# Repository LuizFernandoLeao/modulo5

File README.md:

# Semana 1

Atalho para a página pessoal: [link](https://github.com/LuizFernandoLeao/modulo5/blob/main/semana1/src/pages/my-markdown-page.md)

# Website

This website is built using [Docusaurus](https://docusaurus.io/), a modern static website generator.

### Installation

```
$ yarn
```

### Local Development

```
$ yarn start
```

This command starts a local development server and opens up a browser window. Most changes are reflected live without having to restart the server.

### Build

```
$ yarn build
```

This command generates static content into the `build` directory and can be served using any static contents hosting service.

### Deployment

Using SSH:

```
$ USE_SSH=true yarn deploy
```

Not using SSH:

```
$ GIT_USER=<Your GitHub username> yarn deploy
```

If you are using GitHub pages for hosting, this command is a convenient way to build the website and push to the `gh-pages` branch.

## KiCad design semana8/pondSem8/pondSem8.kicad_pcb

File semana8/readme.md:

# Atividade Ponderada - PCB c/ Raspberry Pi Pico

### Luiz Fernando Leão

## 📜 Descrição

&emsp;Está é a atividade ponderada da semana 8. Esta atividade tem por objetivo desenvolver uma placa de circuito impresso capaz de receber um Raspberry Pi Pico W encaixado utilizando um dispositivo conector, além de um hardware para acionar uma interface de potência (relé e transistor), um dispositivo sinalizador (LED ou Buzzer) e um dispositivo de entrada (analógico ou digital).

&emsp;Esta placa foi construída utilizando o software de CAD para placas eletrônicas utilizado no módulo vigente, além de prototipada utilizando as ferramentas disponíveis no laboratório da instituição, com o intúito de compreender o processo de construção de placas auxiliares de circuito eletrônico.

## 🔴 Vídeo de funcionameto

&emsp; Segue o <a href="https://youtu.be/jeVZRRL9maA">LINK</a> do vídeo com demonstração do funcionamento da placa em protoboard

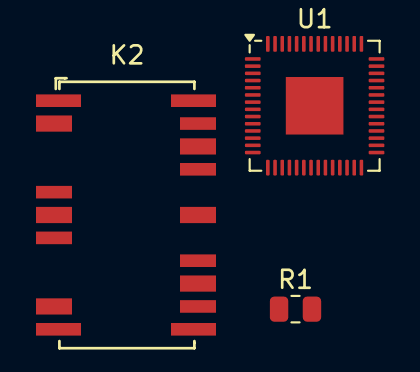
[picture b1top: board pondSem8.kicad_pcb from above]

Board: 2 copper layers, 3 parts (0 on the bottom side), 5 nets, no tracks yet.

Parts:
K2: HF3-53; Relay_SPDT_AXICOM_HF3Series_50ohms_Pitch1.27mm
R1: 220R; R_0805_2012Metric
U1: RP2040; QFN-56-1EP_7x7mm_P0.4mm_EP3.2x3.2mm

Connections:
GND: K2.2 (GND), K2.5 (GND), K2.7 (GND), K2.10 (GND), K2.12 (GND), K2.13 (GND), K2.15 (GND), K2.17 (GND), K2.19 (GND), K2.21 (GND), K2.22 (GND)
unnamed: K2.20, R1.2
unnamed: U1.23 (DVDD), U1.50 (DVDD)
unnamed: K2.6, U1.27 (GPIO16)
unnamed: U1.1 (IOVDD), U1.10 (IOVDD), U1.22 (IOVDD), U1.33 (IOVDD), U1.42 (IOVDD), U1.49 (IOVDD)

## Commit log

2024-02-07 instalação dos pacotes
2024-02-07 instalação de pacotes
2024-02-07 construção da página pessoal
2024-02-07 ajustes na página pessoal
2024-02-07 ajustes no readme
2024-02-07 Remoção das partes não utilizadas no documento do Docusaurus
2024-02-15 ajustes na pagina pessoal
2024-02-15 ajustes no github actions
2024-02-15 ajuste na base url
2024-02-15 ajustes da documentacao
2024-03-02 feat: ponderada semana 3
2024-03-02 pequena correção readme
2024-03-08 feat: prova
2024-03-08 fix: pequenas correções
2024-03-08 fix: mais pequenas correções
2024-03-26 docs: readme semana 8
2024-03-26 fix: readme semana 8
2024-03-27 feat: desenhos esquemáticos
2024-04-03 rascunho inicial
2024-04-04 feat: códigos do dobot
2024-04-05 feat: desenvolvimento dos códigos e ajustes
2024-04-05 feat: prova 2
2024-04-05 fix: ajustes prova
2024-04-05 fix: readme
2024-09-16 docs: plugin image zoom
2024-09-16 docs: ajuste theme config
